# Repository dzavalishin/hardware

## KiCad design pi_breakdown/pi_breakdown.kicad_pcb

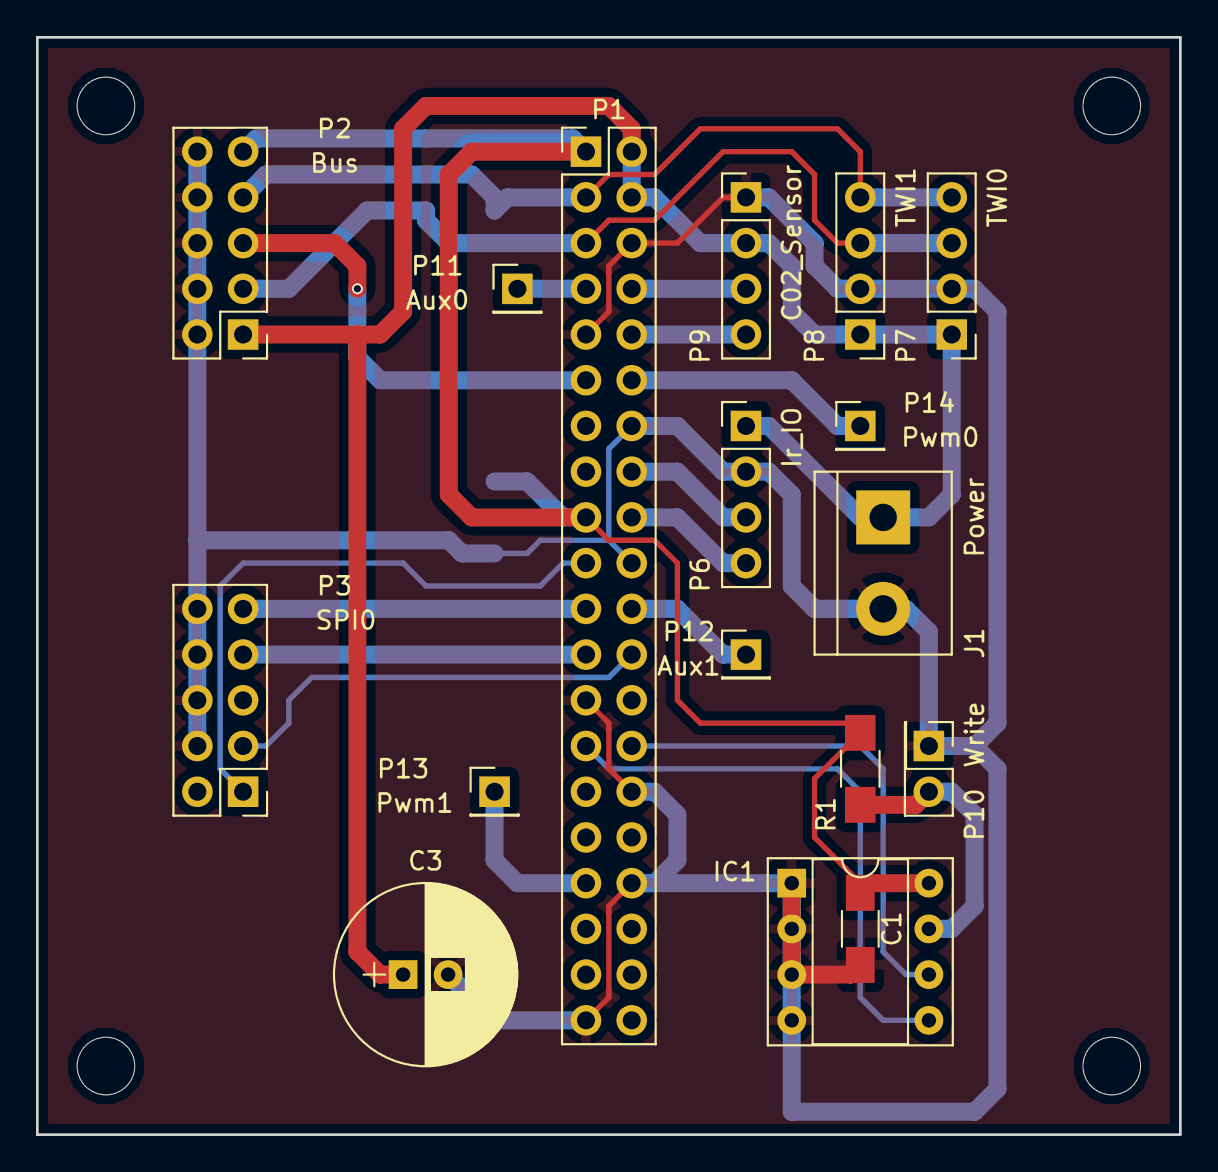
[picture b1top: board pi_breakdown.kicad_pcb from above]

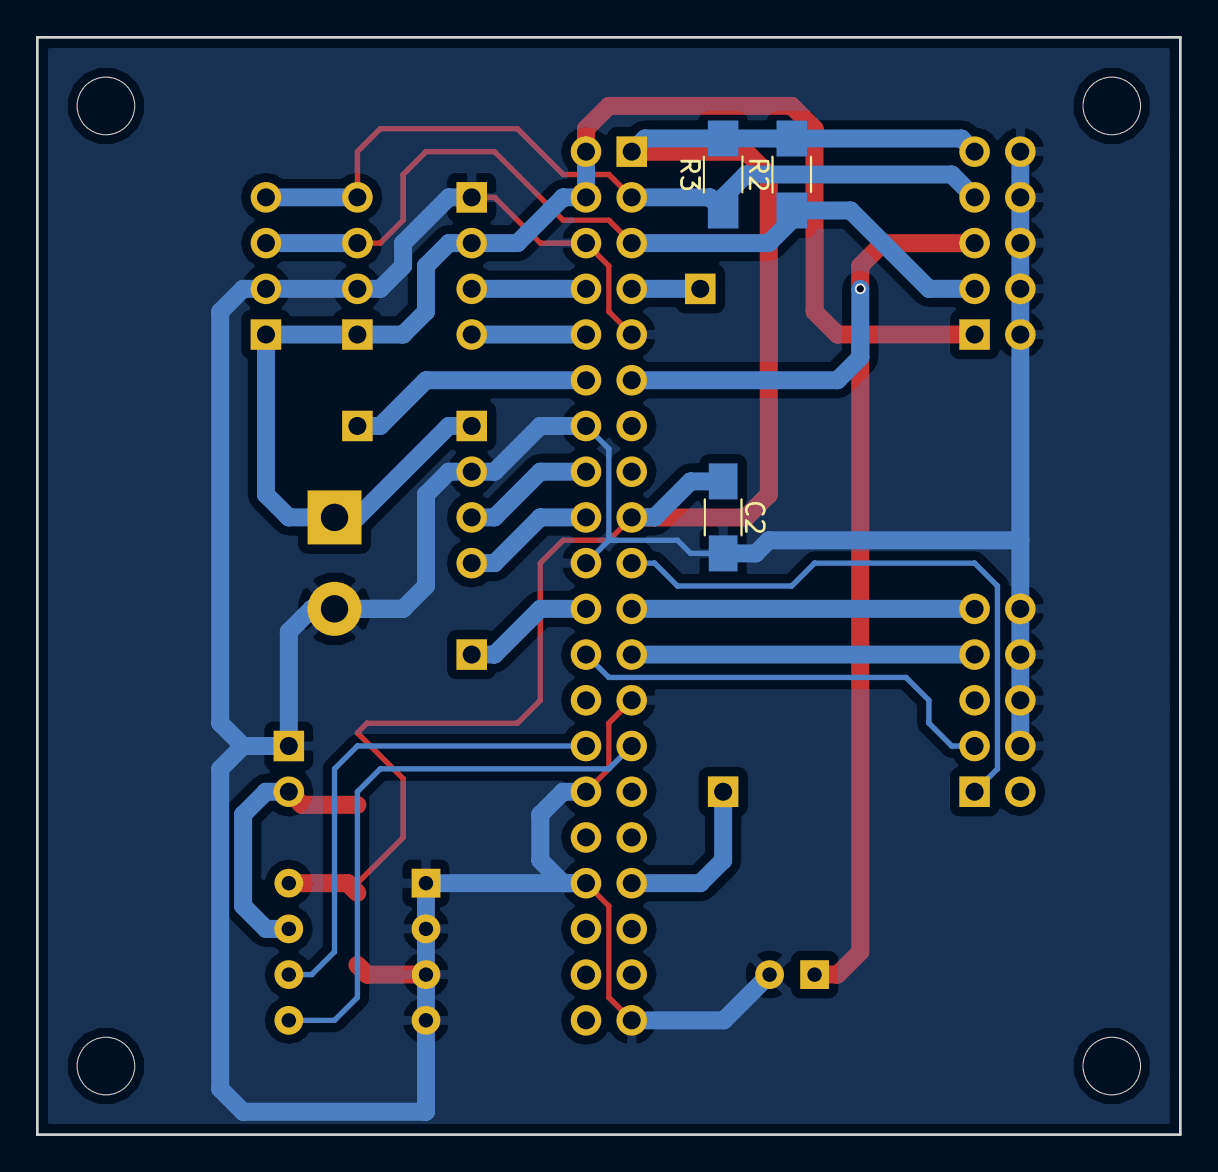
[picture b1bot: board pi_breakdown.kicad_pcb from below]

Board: 2 copper layers, 63.5 x 61.0 mm, 20 parts (3 on the bottom side), 21 nets.

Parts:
C1, C2: 0,1; C_1206_HandSoldering
C3: 100,0; CP_Radial_D10.0mm_P2.50mm
IC1: AT24CS32-SSHM; DIP-8_W7.62mm_Socket
J1: Power; TerminalBlock_bornier-2_P5.08mm
P1: CONN_02X20; Pin_Header_Straight_2x20_Pitch2.54mm
P2: Bus; Pin_Header_Straight_2x05_Pitch2.54mm
P3: SPI0; Pin_Header_Straight_2x05_Pitch2.54mm
P6: Ir_IO; Pin_Header_Straight_1x04_Pitch2.54mm
P7: TWI0; Pin_Header_Straight_1x04_Pitch2.54mm
P8: TWI1; Pin_Header_Straight_1x04_Pitch2.54mm
P9: C02_Sensor; Pin_Header_Straight_1x04_Pitch2.54mm
P10: Write; Pin_Header_Straight_2x01_Pitch2.54mm
P11: Aux0; Pin_Header_Straight_1x01_Pitch2.54mm
P12: Aux1; Pin_Header_Straight_1x01_Pitch2.54mm
P13: Pwm1; Pin_Header_Straight_1x01_Pitch2.54mm
P14: Pwm0; Pin_Header_Straight_1x01_Pitch2.54mm
R1: 10k; R_1206_HandSoldering
R2, R3: 4,7k; R_1206_HandSoldering

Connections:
+3V3: C1.1, C2.1, IC1.8, P1.1, P1.17, P2.9, R1.1, R2.2, R3.2
+5V: C3.1, J1.1, P1.2, P1.4, P2.1, P6.1, P7.1, P8.1, P9.2
/1W: P1.11, P2.5
/ID_SC: IC1.6, P1.28
/ID_SD: IC1.5, P1.27
/Ir_RX: P1.16, P6.3
/Ir_TX: P1.18, P6.4
/MISO: P1.21, P3.9
/MOSI: P1.19, P3.1
/PWM0: P1.12, P14.1
/PWM1: P1.33, P13.1
/RxD: P1.10, P9.4
/SCK: P1.23, P3.7
/SCL: P1.5, P2.3, P7.3, P8.3, R2.1
/SDA: P1.3, P2.7, P7.4, P8.4, R3.1
/SS0: P1.24, P3.3
/TxD: P1.8, P9.3
GND: C1.2, C2.2, C3.2, IC1.1, IC1.2, IC1.3, IC1.4, J1.2, P1.6, P1.9, P1.14, P1.20, P1.25, P1.30, P1.34, P1.39, P2.2, P2.4, P2.6, P2.8, P2.10, P3.4, P3.6, P3.8, P3.10, P6.2, P7.2, P8.2, P9.1, P10.1
unnamed: IC1.7, P10.2, R1.2
unnamed: P1.7, P11.1
unnamed: P1.22, P12.1

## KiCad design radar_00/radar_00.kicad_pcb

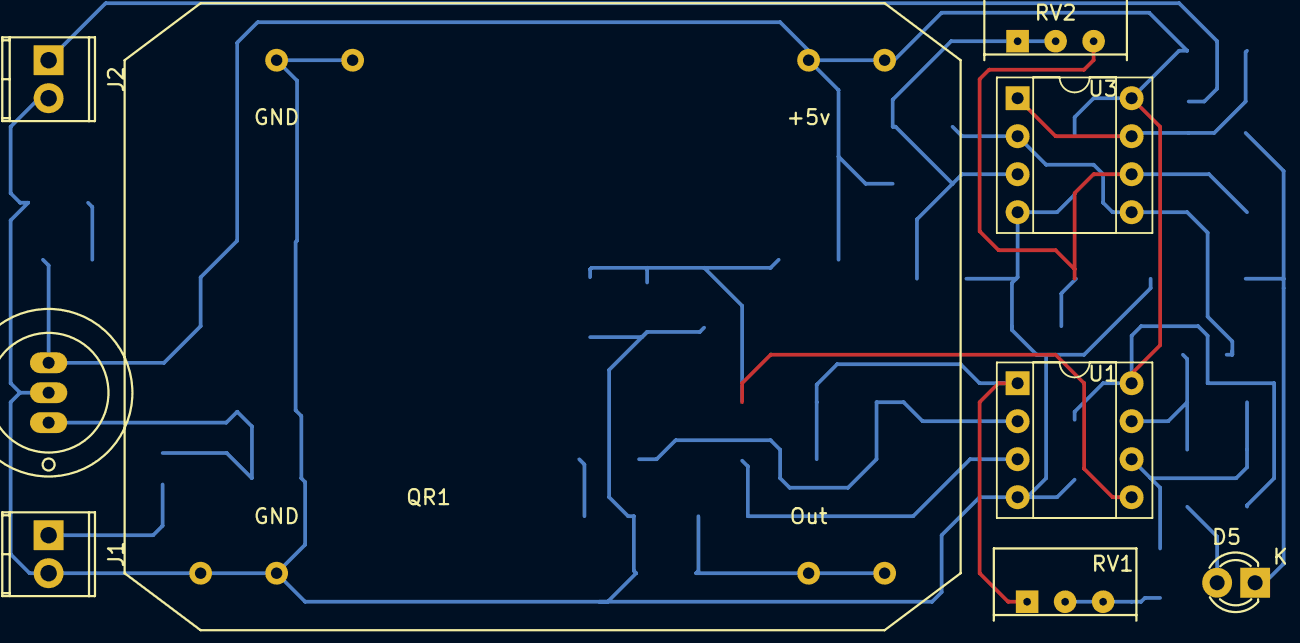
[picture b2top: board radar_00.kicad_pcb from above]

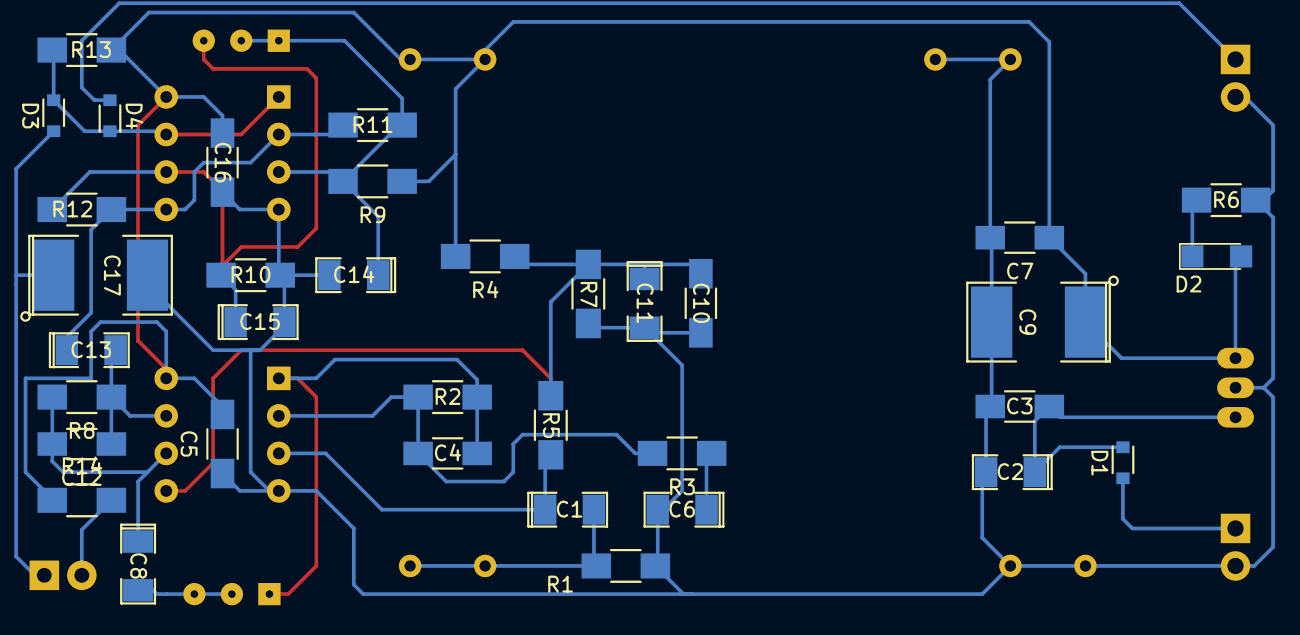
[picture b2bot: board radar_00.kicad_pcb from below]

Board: 2 copper layers, 44 parts (35 on the bottom side), 21 nets.

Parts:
C1, C6, C8, C11, C13, C14, C15: 10,0; SMD-1206_Pol
C2: 47,0; SMD-1206_Pol
C3, C5, C7, C10, C16: 0,1; C_1206_HandSoldering
C4, C12: 2200; C_1206_HandSoldering
C9: 220,0; SMD-2112_Pol
C17: 100,0; SMD-2112_Pol
D1, D3, D4: D; D_0805
D2: LED; LED_1206
D5: LED; LED-3MM
J1, J2: Screw_Terminal_1x02; TerminalBlock_Pheonix_MPT-2.54mm_2pol
QR1: HB-100-Radar
R1: 13k; R_1206_HandSoldering
R2, R8: 1M; R_1206_HandSoldering
R3: R; R_1206_HandSoldering
R4, R7, R11, R12: 47k; R_1206_HandSoldering
R5: 200k; R_1206_HandSoldering
R6: 2,2k; R_1206_HandSoldering
R9, R10, R13: 4,7k; R_1206_HandSoldering
R14: 1,0k; R_1206_HandSoldering
RV1: 47k; Potentiometer_Trimmer-Suntan-TSR-3386C
RV2: 510; Potentiometer_Trimmer-Suntan-TSR-3386C
U1: LM358; DIP-8_W7.62mm_Socket
U2: 78L05; OldSowjetaera_Transistor_Type-I_BigPads
U3: LM2903; DIP-8_W7.62mm_Socket

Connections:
+5V: C5.2, C7.1, C9.1, C16.2, D2.2, QR1.7, QR1.8, R4.2, R9.1, R13.1, R14.1, U1.8, U2.3, U3.8
GND: C2.2, C3.2, C5.1, C6.2, C7.2, C9.2, C10.1, C11.2, C14.2, C15.2, C16.1, C17.2, J1.2, J2.2, QR1.1, QR1.2, QR1.3, QR1.4, R1.2, R6.1, R7.1, R10.2, U1.4, U2.2, U3.4
unnamed: C1.1, R5.2, U1.3
unnamed: C1.2, QR1.5, QR1.6, R1.1
unnamed: C2.1, C3.1, D1.1, U2.1
unnamed: C4.1, R2.1, RV1.1, U1.1
unnamed: C4.2, R2.2, R3.2, U1.2
unnamed: C6.1, R3.1
unnamed: C8.2, RV1.2, RV1.3
unnamed: C10.2, C11.1, R4.1, R5.1, R7.2, U1.5
unnamed: C12.1, C13.2, R8.1, U1.7
unnamed: C8.1, C12.2, R8.2, U1.6
unnamed: C13.1, R11.1, R12.1, U3.2, U3.5
unnamed: C14.1, R9.2, R11.2, RV2.1, RV2.2, U3.3
unnamed: C15.1, R10.1, R12.2, RV2.3, U3.6
unnamed: C17.1, D3.2, D5.1
unnamed: D1.2, J1.1
unnamed: D2.1, R6.2
unnamed: D3.1, D4.1, R13.2, U3.1, U3.7
unnamed: D4.2, J2.1
unnamed: D5.2, R14.2

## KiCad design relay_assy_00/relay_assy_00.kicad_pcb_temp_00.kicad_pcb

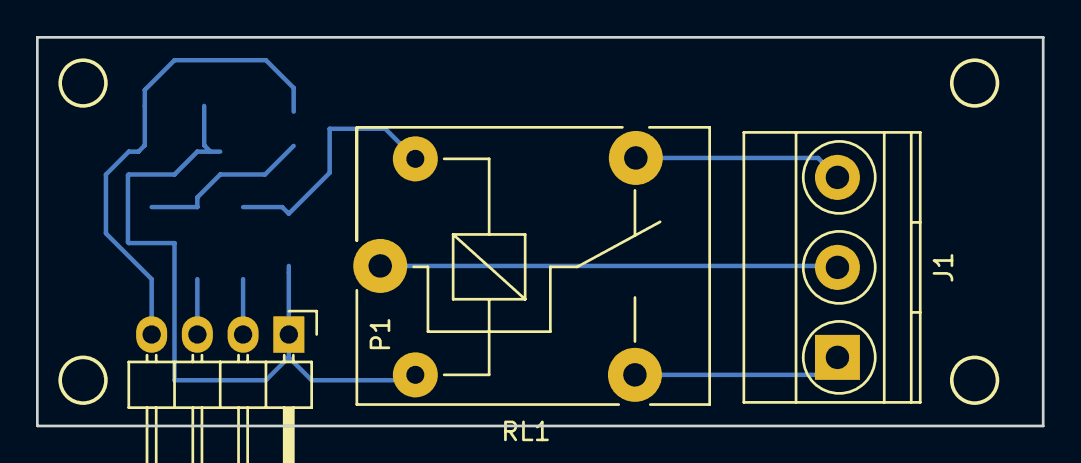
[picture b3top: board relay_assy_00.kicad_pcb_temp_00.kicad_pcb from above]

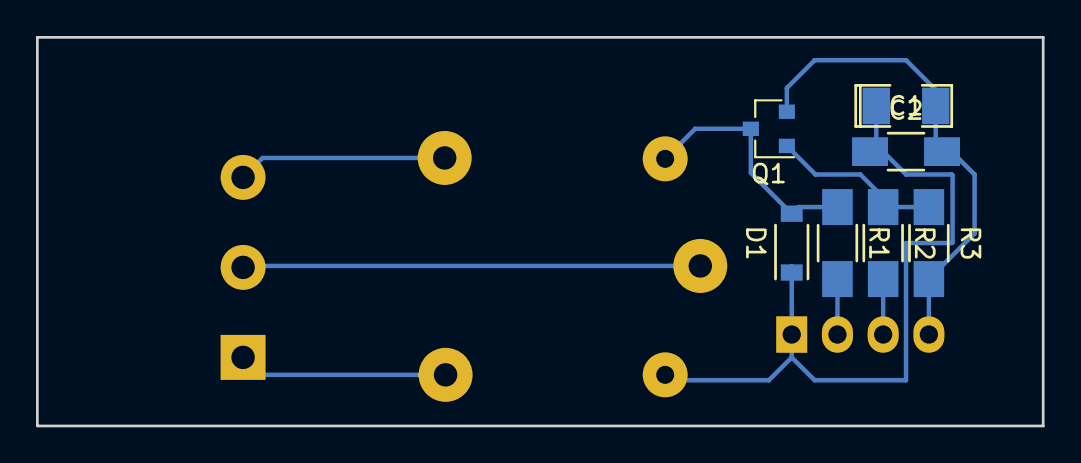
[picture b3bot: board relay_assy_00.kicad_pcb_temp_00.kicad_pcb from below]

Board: 2 copper layers, 55.9 x 21.6 mm, 10 parts (7 on the bottom side), 9 nets.

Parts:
C1: 10,0; SMD-1206_Pol
C2: 0,1; C_1206_HandSoldering
D1: 1N4148W; SOD-123
J1: Screw_Terminal_1x03; TerminalBlock_Pheonix_MKDS1.5-3pol
P1: CONN_01X04; Pin_Header_Angled_1x04
Q1: BC817-40; SOT-23
R1: 1k; R_1206_HandSoldering
R2: 560; R_1206_HandSoldering
R3: 10k; R_1206_HandSoldering
RL1: RM50-xx11; Relay_SANYOU_SRD_Series_Form_C

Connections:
GND: C1.2, C2.2, P1.4, Q1.2, R3.2
unnamed: C1.1, C2.1, D1.1, P1.1, RL1.2
unnamed: D1.2, Q1.3, R1.1, RL1.5
unnamed: J1.1, RL1.3
unnamed: J1.2, RL1.1
unnamed: J1.3, RL1.4
unnamed: P1.3, R2.2
unnamed: Q1.1, R2.1, R3.1
unnamed: P1.2, R1.2

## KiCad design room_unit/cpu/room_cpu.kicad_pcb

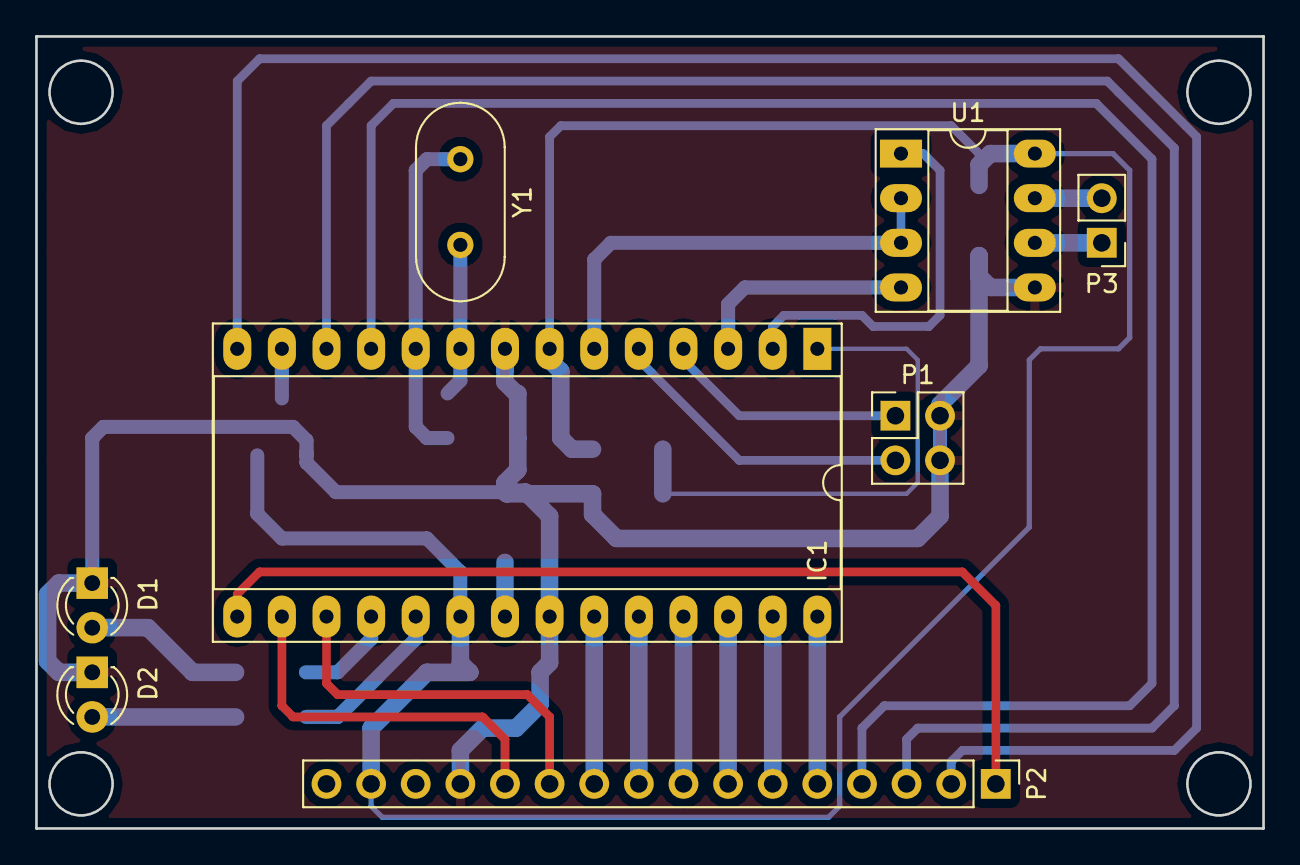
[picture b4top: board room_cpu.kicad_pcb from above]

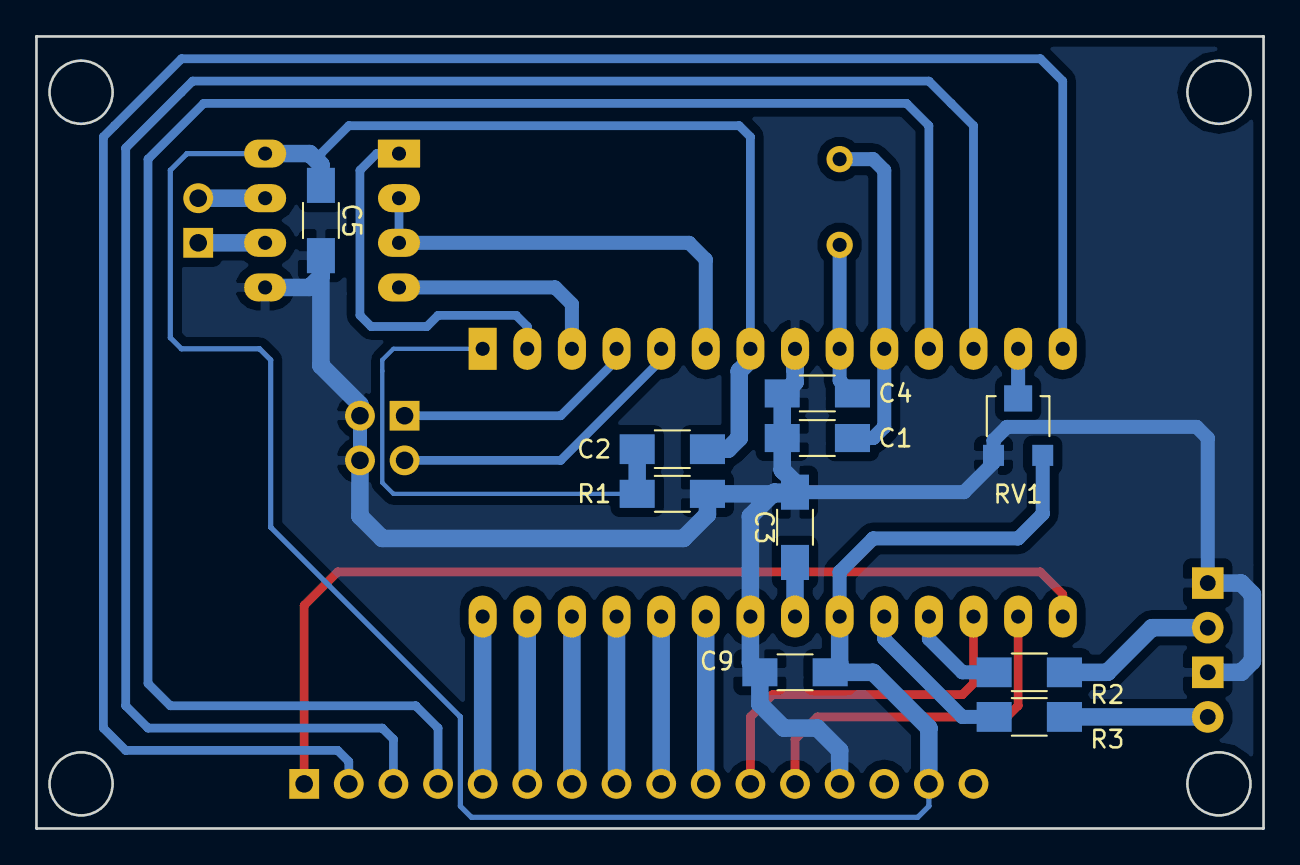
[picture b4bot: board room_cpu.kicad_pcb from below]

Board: 2 copper layers, 69.8 x 45.1 mm, 18 parts (10 on the bottom side), 30 nets.

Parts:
C1, C4: 18pF; C_1206_HandSoldering
C2, C3: 1,0; C_1206_HandSoldering
C5, C9: 0,1; C_1206_HandSoldering
D1: IO; LED_D3.0mm
D2: Fail; LED_D3.0mm
IC1: ATMEGA8-P; DIP-28_W15.24mm_Socket_LongPads
P1: ModbusAddrL; Pin_Header_Straight_2x02_Pitch2.54mm
P2: Bus; Pin_Header_Straight_1x16_Pitch2.54mm
P3: RS485; Pin_Header_Straight_1x02_Pitch2.54mm
R1: 1k; R_1206_HandSoldering
R2, R3: 2,2k; R_1206_HandSoldering
RV1: Comparator; Potentiometer_Trimmer-EVM3E
U1: ST485; DIP-8_W7.62mm_Socket_LongPads
Y1: 16MHz; Crystal_HC49-U_Vertical

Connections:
+5V: C5.1, C9.2, IC1.7, IC1.20, P2.15, R1.1, RV1.3, U1.8
/1Wire: IC1.16, P2.12
/AI0: IC1.23, P2.10
/AI1: IC1.24, P2.9
/AI2: IC1.25, P2.8
/AI3: IC1.26, P2.7
/DI0: IC1.11, P2.4
/DI1: IC1.12, P2.3
/DO0: IC1.14, P2.2
/DO1: IC1.15, P2.1
/DO2: IC1.17, P2.11
/Fail_Led: IC1.19, R3.2
/IO_Led: IC1.18, R2.2
/Reset: C2.1, IC1.1, R1.2
/Rx: IC1.2, U1.1
/SCL: IC1.28, P2.5
/SDA: IC1.27, P2.6
/Tx: IC1.3, U1.4
/TxE: IC1.6, U1.2, U1.3
GND: C1.2, C2.2, C3.2, C4.2, C5.2, C9.1, D1.1, D2.1, IC1.8, IC1.22, P1.2, P1.4, P2.13, RV1.1, U1.5
unnamed: C1.1, IC1.10, Y1.1
unnamed: C3.1, IC1.21
unnamed: C4.1, IC1.9, Y1.2
unnamed: D1.2, R2.1
unnamed: D2.2, R3.1
unnamed: IC1.4, P1.1
unnamed: IC1.5, P1.3
unnamed: IC1.13, RV1.2
unnamed: P3.1, U1.6
unnamed: P3.2, U1.7

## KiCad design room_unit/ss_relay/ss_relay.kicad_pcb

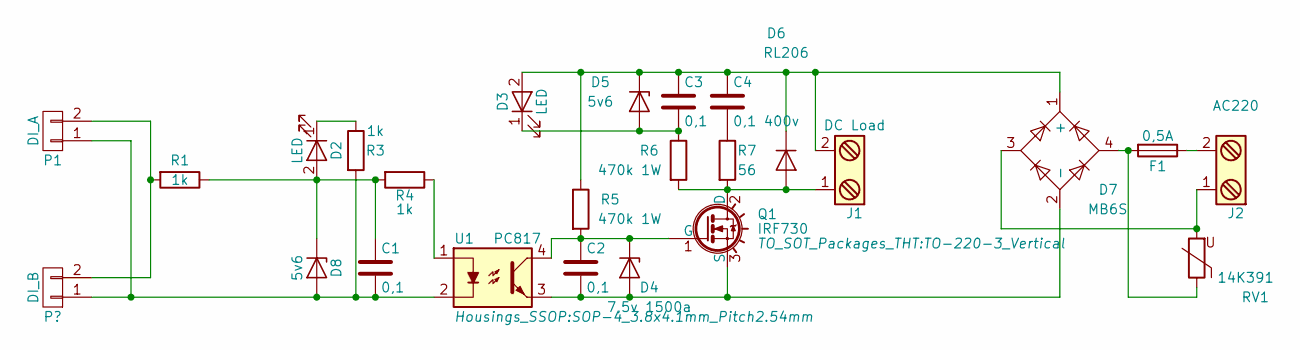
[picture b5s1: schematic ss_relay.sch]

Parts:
C1, C2, C3: 0,1; C_1206_HandSoldering
C4: 0,1 400v; C_Rect_L10.3mm_W5.0mm_P7.50mm_MKS4
D2, D3: LED; LED_D3.0mm
D4: 7,5v 1500a; D_DO-201AD_P5.08mm_Vertical_KathodeUp
D5, D8: 5v6; D_1206
D6: RL206; D_DO-15_P5.08mm_Vertical_AnodeUp
D7: MB6S; Diode_Bridge_TO-269AA
F1: 0,5A; Fuseholder5x20_horiz_open_inline_Type-I
J1: DC Load; TerminalBlock_Pheonix_MPT-2.54mm_2pol
J2: AC220; TerminalBlock_Pheonix_MPT-2.54mm_2pol
P1: DI_A; Pin_Header_Straight_1x02_Pitch2.54mm
Q1: IRF730; TO-220-3_Vertical
R1, R3, R4: 1k; R_1206_HandSoldering
R5, R6: 470k 1W; R_Axial_DIN0617_L17.0mm_D6.0mm_P20.32mm_Horizontal
R7: 56; R_Axial_DIN0617_L17.0mm_D6.0mm_P20.32mm_Horizontal
RV1: 14K391; RV_Disc_D21.5_W4.3_P10
U1: PC817; SOP-4_3.8x4.1mm_Pitch2.54mm

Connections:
unnamed: C1.1, D2.2 (A), D8.1 (K), R1.1, R4.2
unnamed 1: C1.2, D8.2 (A), P1.1, R3.2, U1.2; also elsewhere on the board
unnamed: C2.1, D4.1 (K), Q1.1 (G), R5.2, U1.4
unnamed: C2.2, D4.2 (A), D7.2 (-), Q1.3 (S), U1.3
unnamed: C3.1, C4.1, D3.2 (A), D5.1 (K), D6.1 (K), D7.1 (+), J1.2, R5.1
unnamed: C3.2, D3.1 (K), D5.2 (A), R6.1
unnamed: C4.2, R7.1
unnamed: D2.1 (K), R3.1
unnamed: D6.2 (A), J1.1, Q1.2 (D), R6.2, R7.2
unnamed: D7.3, J2.1, RV1.2
unnamed: D7.4, F1.2, RV1.1
unnamed: F1.1, J2.2
unnamed 12: P1.2, R1.2; also elsewhere on the board
unnamed: R4.1, U1.1

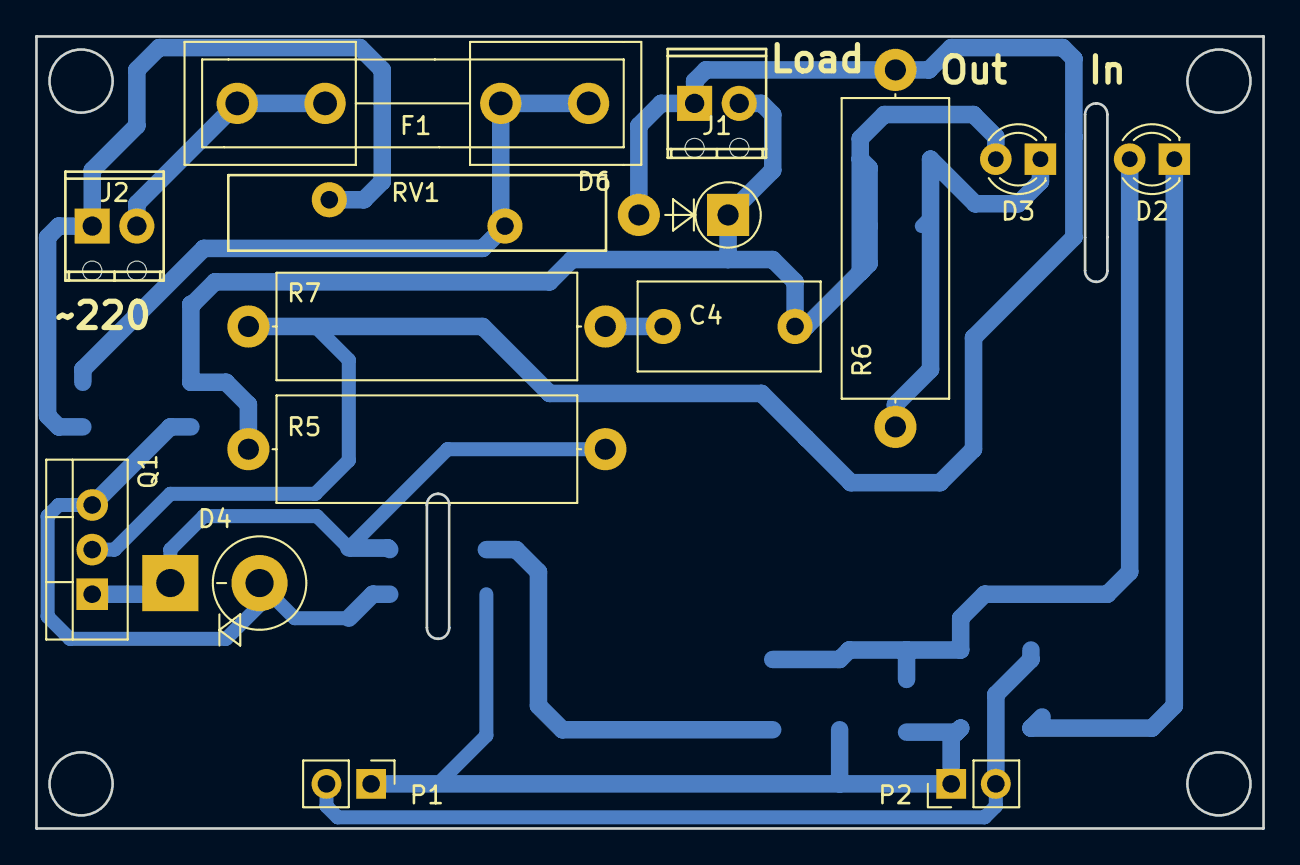
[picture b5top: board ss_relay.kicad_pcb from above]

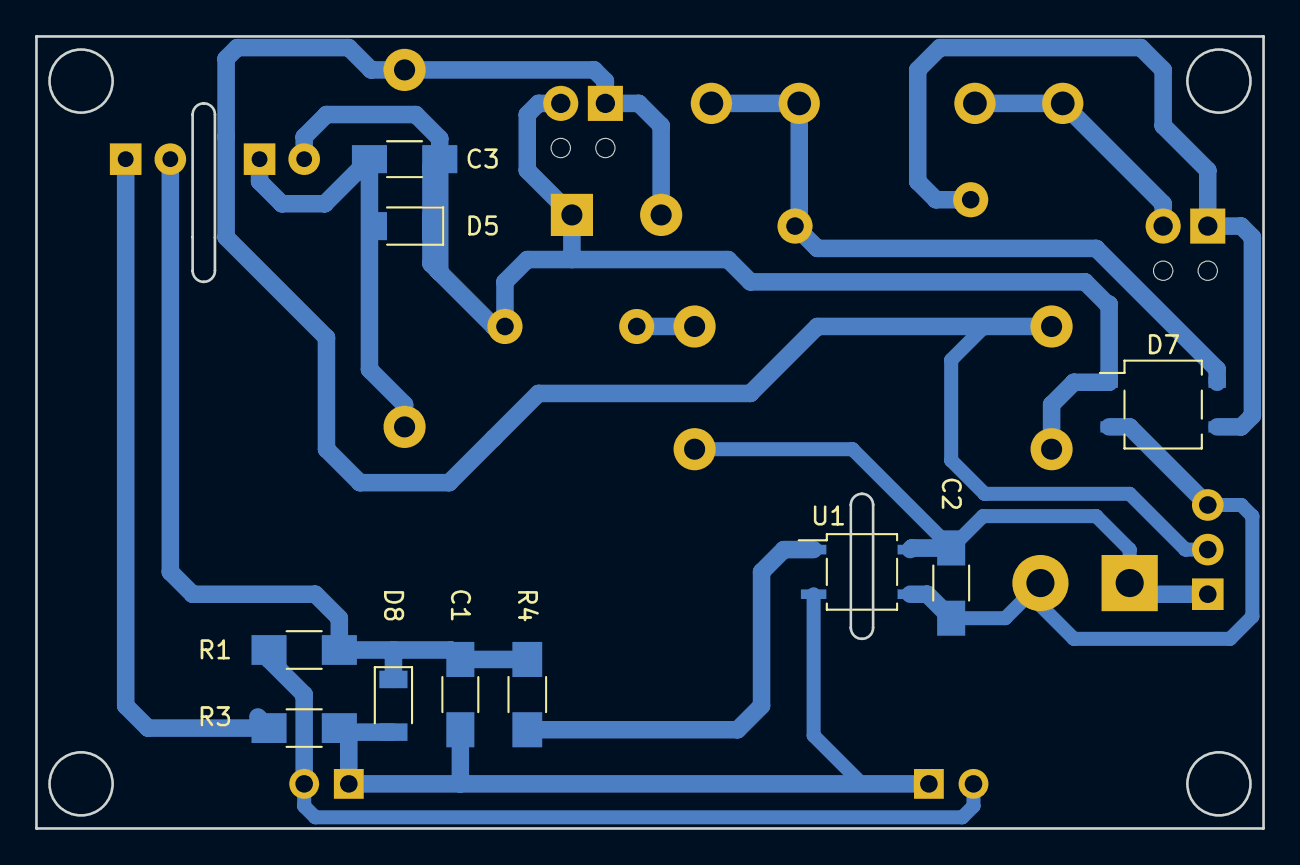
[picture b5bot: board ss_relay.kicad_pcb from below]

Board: 2 copper layers, 69.9 x 45.1 mm, 25 parts (10 on the bottom side), 14 nets.

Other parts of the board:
P2: DI_B; Pin_Header_Straight_1x02_Pitch2.54mm

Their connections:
unnamed 1: P2.1; also elsewhere on the board
unnamed 12: P2.2; also elsewhere on the board
